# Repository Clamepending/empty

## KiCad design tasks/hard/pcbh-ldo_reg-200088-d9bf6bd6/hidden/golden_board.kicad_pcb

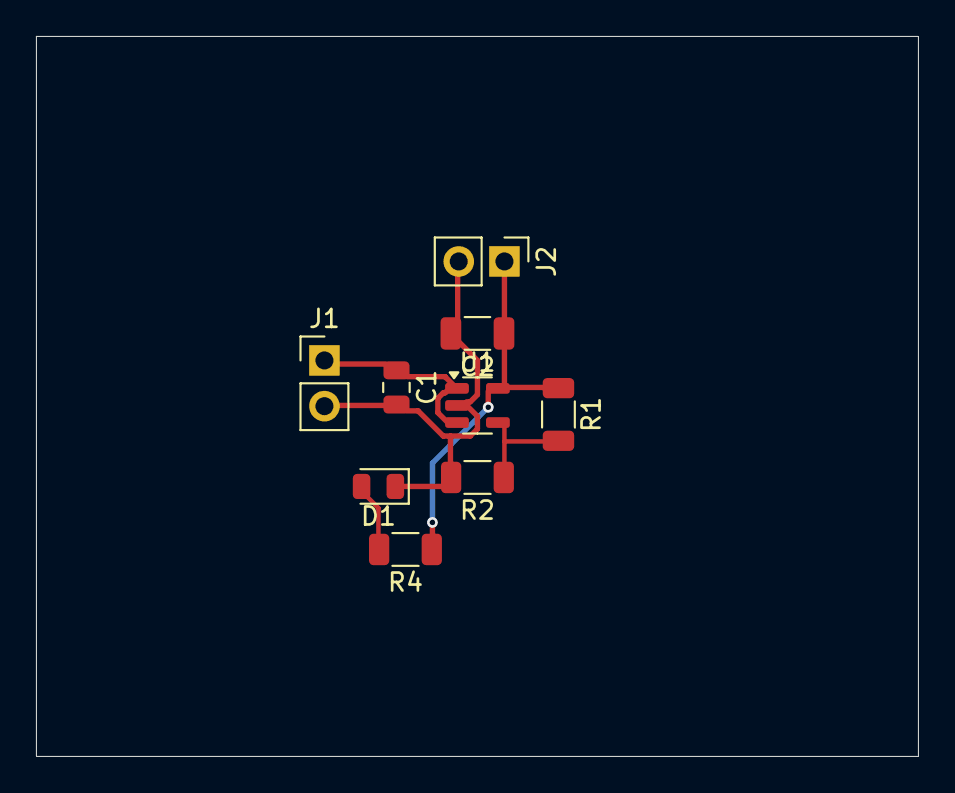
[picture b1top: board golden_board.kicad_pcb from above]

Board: 2 copper layers, 49.0 x 40.0 mm, 9 parts (0 on the bottom side), 5 nets.

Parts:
C1: 1u; C_0805_2012Metric
C2: 4.7u; C_1206_3216Metric
D1: LED_0805_2012Metric
J1, J2: PinHeader_1x02_P2.54mm_Vertical
R1: 73.2k; R_1206_3216Metric
R2: 23.7k; R_1206_3216Metric
R4: 1.5k; R_1206_3216Metric
U1: SOT-23-5

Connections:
+3V3: C2.1, J2.1, R1.1, R4.1, U1.5
FB: R1.2, R2.1, U1.4
GND: C1.2, C2.2, D1.1, J1.2, J2.2, R2.2, U1.2
LED: D1.2, R4.2
VIN: C1.1, J1.1, U1.1, U1.3

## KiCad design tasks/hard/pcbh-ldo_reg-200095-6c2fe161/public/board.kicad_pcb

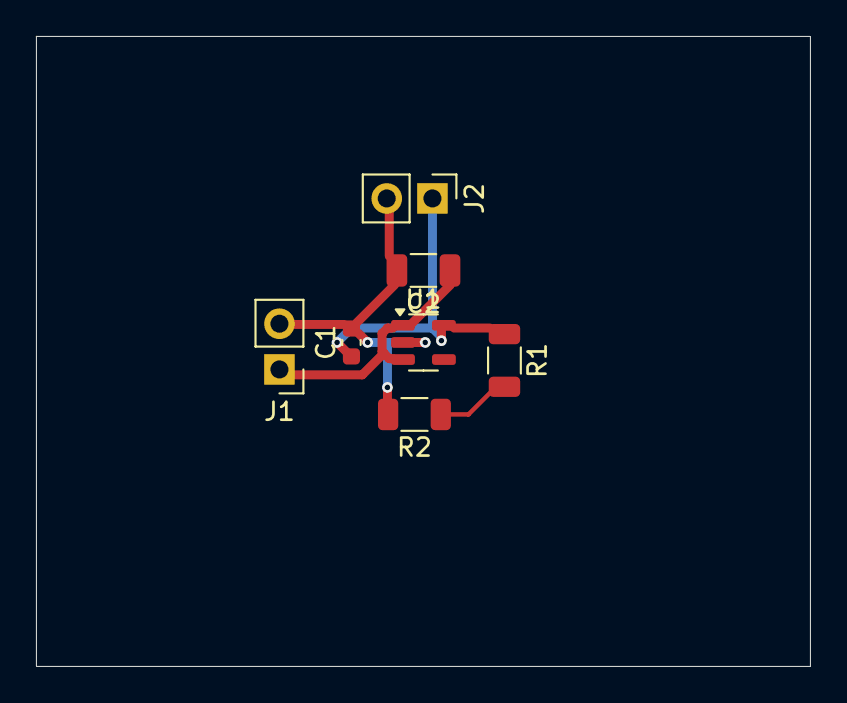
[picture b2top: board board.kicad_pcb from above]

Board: 2 copper layers, 43.0 x 35.0 mm, 7 parts (0 on the bottom side), 4 nets.

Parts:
C1: 10u; C_0603_1608Metric
C2: 2.2u; C_1206_3216Metric
J1, J2: PinHeader_1x02_P2.54mm_Vertical
R1: 61.9k; R_1206_3216Metric
R2: 49.9k; R_1206_3216Metric
U1: SOT-23-5

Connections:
+1V8: C1.1, J2.1, R1.1, U1.5
FB: R1.2, R2.1
GND: C1.2, C2.2, J1.2, J2.2, R2.2, U1.2
VIN: C2.1, J1.1, U1.1, U1.3
